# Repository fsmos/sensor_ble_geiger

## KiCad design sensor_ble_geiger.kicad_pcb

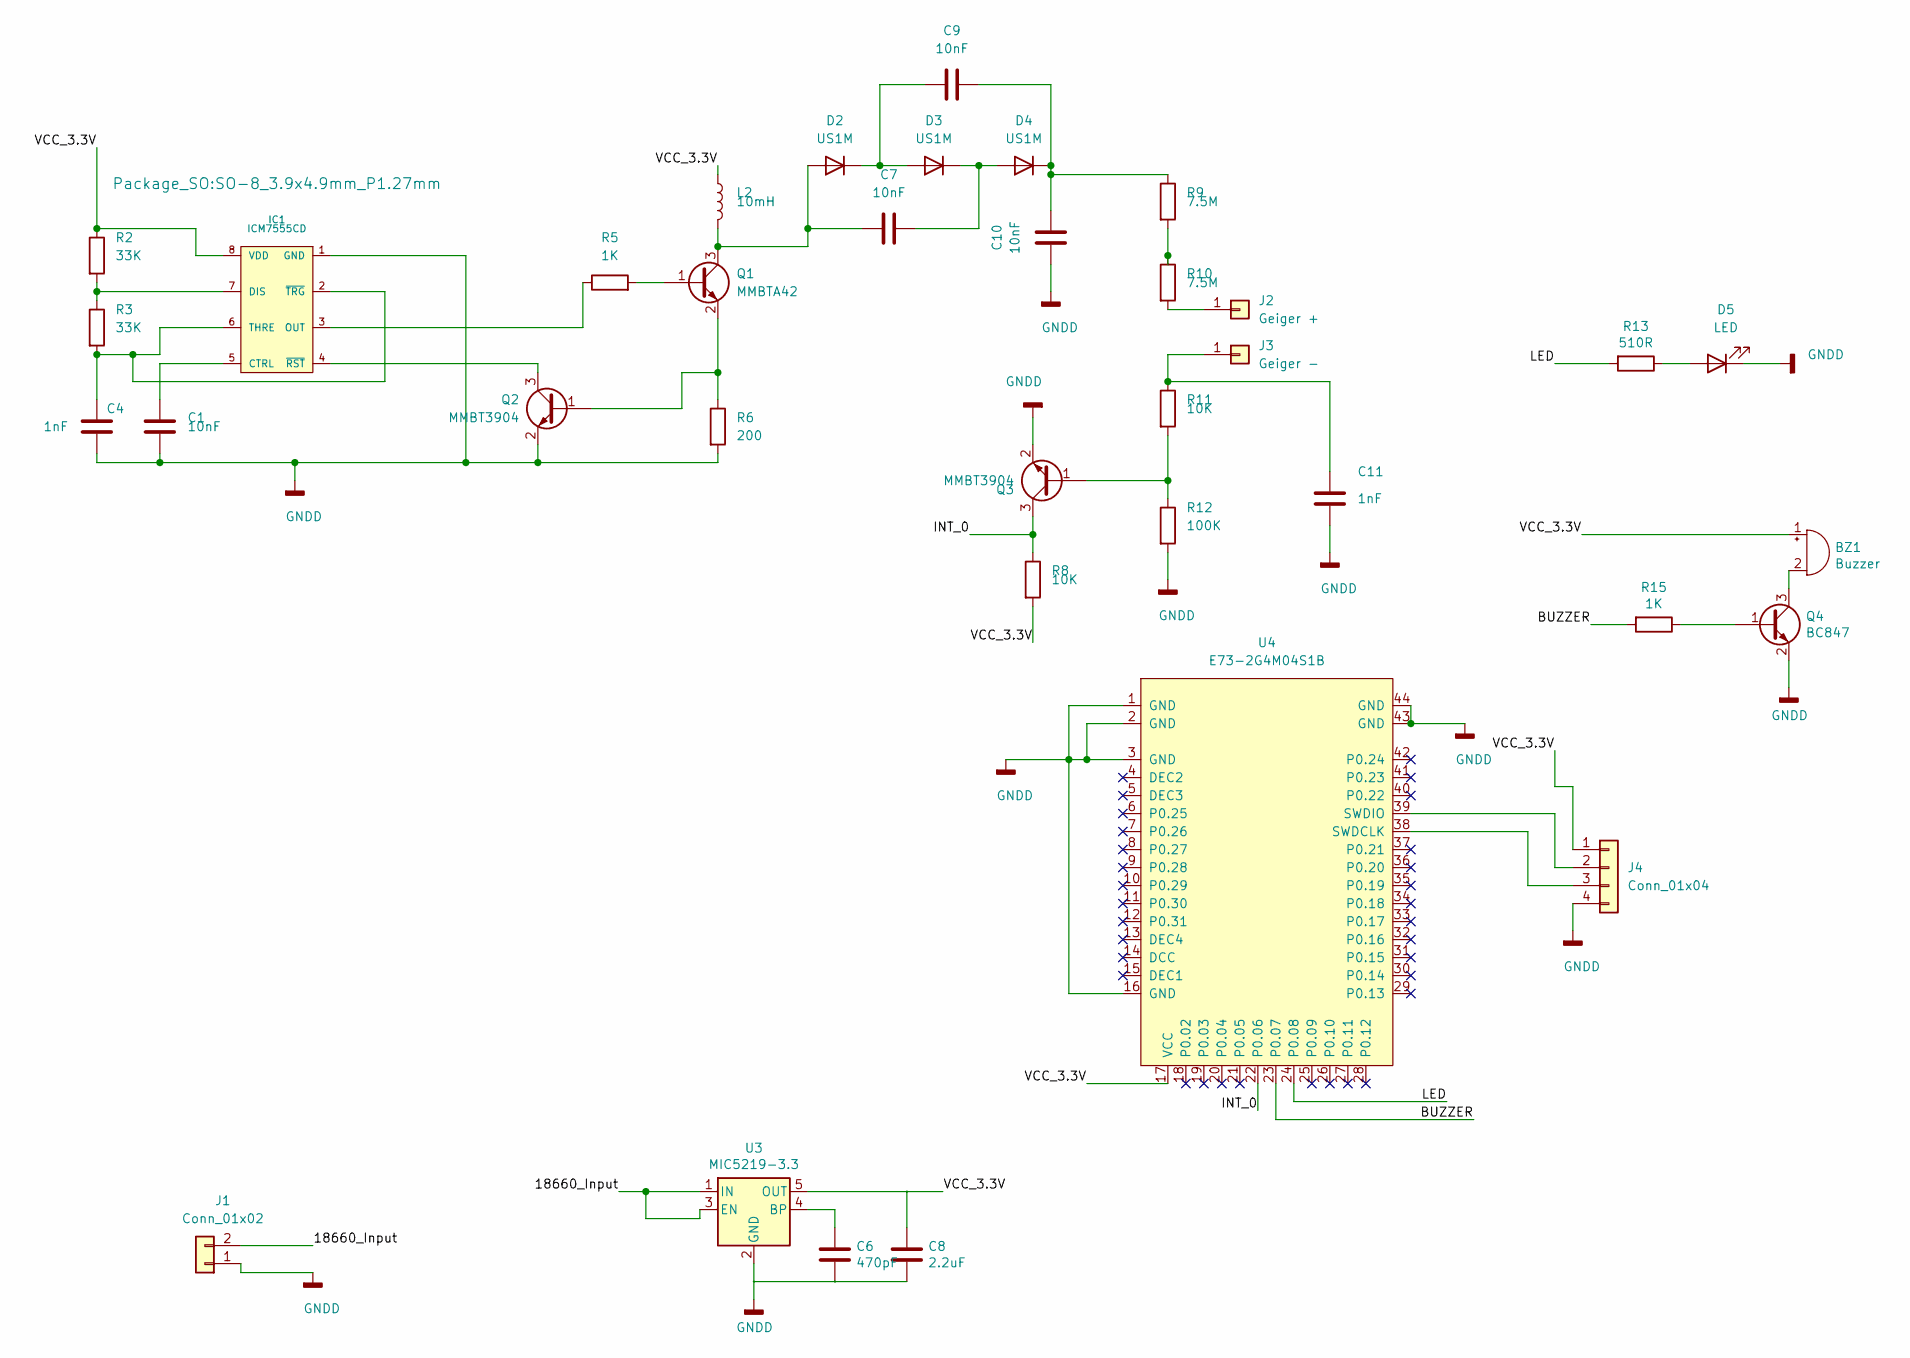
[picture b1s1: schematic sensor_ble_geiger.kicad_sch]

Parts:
BZ1: Buzzer; Buzzer_15x7.5RM7.6
C1: 10nF; R_0805_2012Metric
C4, C11: 1nF; R_0805_2012Metric
C6: 470pF; C_0805_2012Metric
C7, C9, C10: 10nF; R_1210_3225Metric
C8: 2.2uF; C_0805_2012Metric
D2, D3, D4: US1M; D_SMA
D5: LED; LED_D3.0mm
IC1: ICM7555CD; SO-8_3.9x4.9mm_P1.27mm
J1: Conn_01x02; PinHeader_1x02_P2.54mm_Vertical
J2: Geiger +; Датчик
J3: Geiger -; Датчик
J4: Conn_01x04; PinHeader_1x04_P2.54mm_Horizontal
L2: 10mH; BOURNS-SDR0503
Q1: MMBTA42; SOT-23
Q2, Q3: MMBT3904; SOT-23
Q4: BC847; SOT-23
R2, R3: 33K; R_0805_2012Metric
R5, R15: 1K; R_0805_2012Metric
R6: 200; R_0805_2012Metric
R8, R11: 10K; R_0805_2012Metric
R9, R10: 7.5M; R_0805_2012Metric
R12: 100K; R_0805_2012Metric
R13: 510R; R_0805_2012Metric
U3: MIC5219-3.3; SOT-23-5
U4: E73-2G4M04S1B

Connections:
/18660_Input: J1.2, U3.1 (IN), U3.3 (EN)
/BUZZER: R15.2, U4.23 (P0.07)
/INT_0: Q3.3 (C), R8.1, U4.22 (P0.06)
/LED: R13.2, U4.24 (P0.08)
/VCC_3.3V: BZ1.1 (-), C8.1, IC1.8 (VDD), J4.1, L2.1, R2.1, R8.2, U3.5 (OUT), U4.17 (VCC)
GNDD: C1.2, C4.2, C6.2, C8.2, C10.1, C11.2, D5.1 (K), IC1.1 (GND), J1.1, J4.4, Q2.2 (E), Q3.2 (E), Q4.2 (E), R6.2, R12.2, U3.2 (GND), U4.1 (GND), U4.2 (GND), U4.3 (GND), U4.16 (GND), U4.43 (GND), U4.44 (GND)
unnamed: BZ1.2 (+), Q4.3 (C)
unnamed: C1.1, IC1.5 (CTRL)
unnamed: C4.1, IC1.2 (~TRG), IC1.6 (THRE), R3.2
unnamed: C6.1, U3.4 (BP)
unnamed: C7.1, D2.2 (A), L2.2, Q1.3 (C)
unnamed: C7.2, D3.1 (K), D4.2 (A)
unnamed: C9.1, D2.1 (K), D3.2 (A)
unnamed: C9.2, C10.2, D4.1 (K), R9.1
unnamed: C11.1, J3.1, R11.1
unnamed: D5.2 (A), R13.1
unnamed: J2.1, R10.2
unnamed: J4.2, U4.39 (SWDIO)
unnamed: J4.3, U4.38 (SWDCLK)
unnamed: Q1.1 (B), R5.2
unnamed: Q1.2 (E), Q2.1 (B), R6.1
unnamed: IC1.4 (~RST), Q2.3 (C)
unnamed: Q3.1 (B), R11.2, R12.1
unnamed: Q4.1 (B), R15.1
unnamed: IC1.7 (DIS), R2.2, R3.1
unnamed: IC1.3 (OUT), R5.1
unnamed: R9.2, R10.1

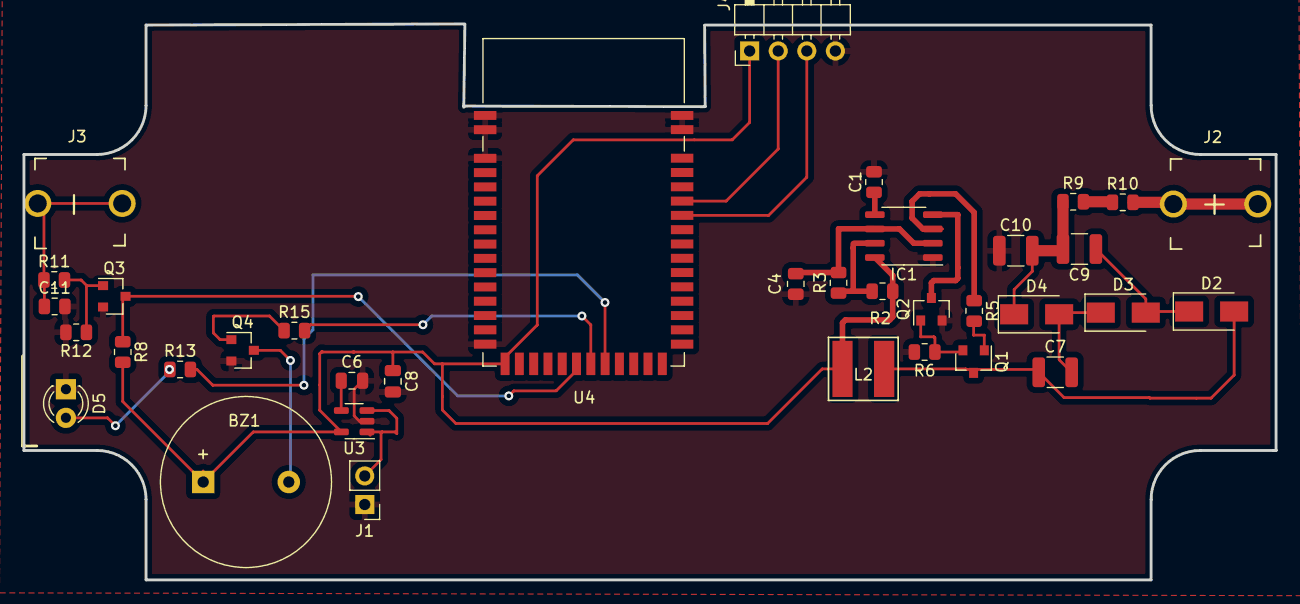
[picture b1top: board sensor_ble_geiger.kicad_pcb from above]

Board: 2 copper layers, 111.3 x 49.4 mm, 36 parts (0 on the bottom side), 27 nets.

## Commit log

2020-11-30 power source
2020-12-05 Добавлена разводка
2020-12-19 Move to 3.3V
